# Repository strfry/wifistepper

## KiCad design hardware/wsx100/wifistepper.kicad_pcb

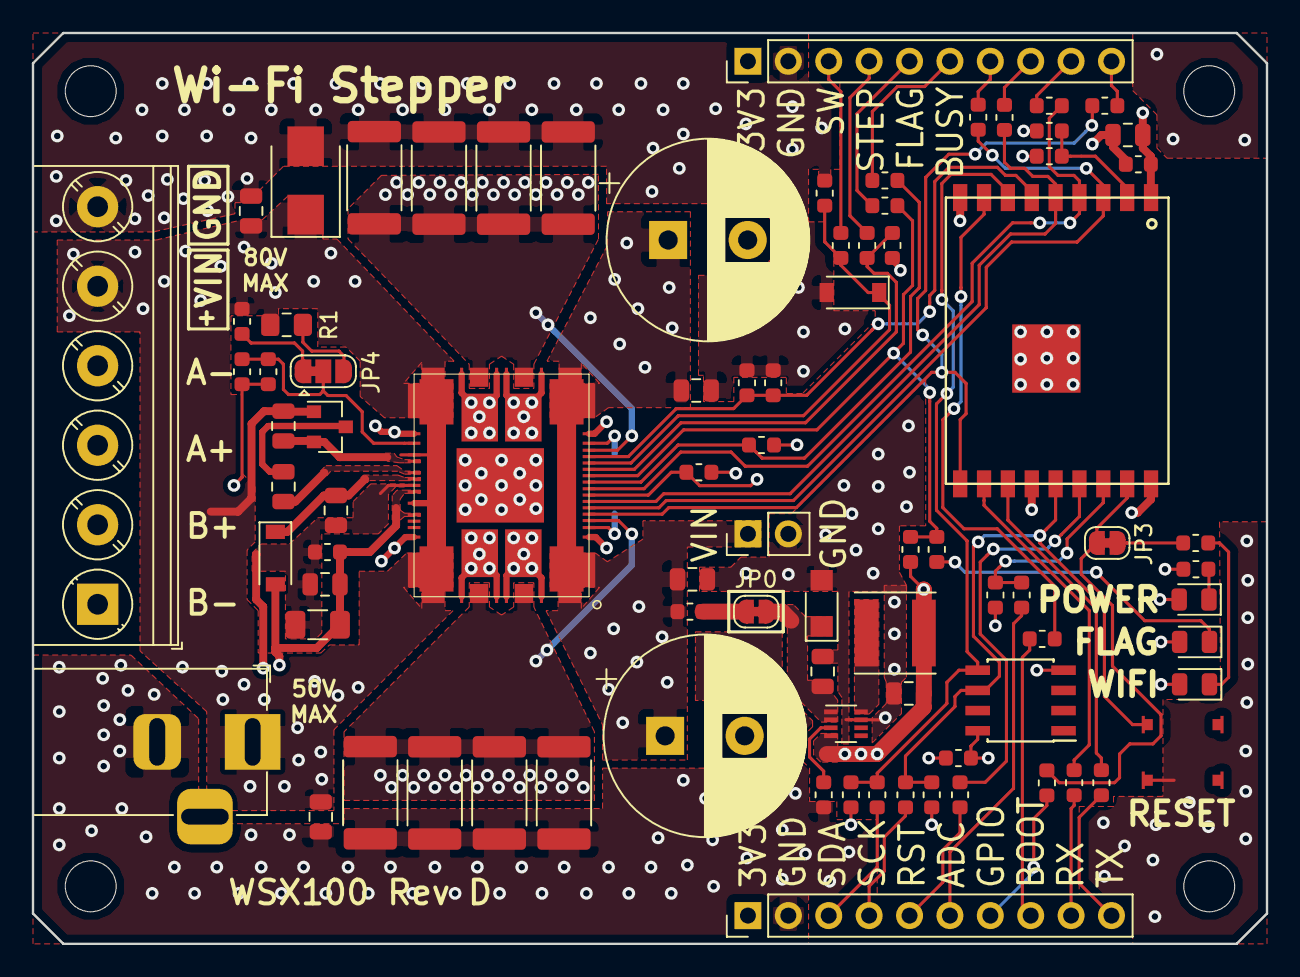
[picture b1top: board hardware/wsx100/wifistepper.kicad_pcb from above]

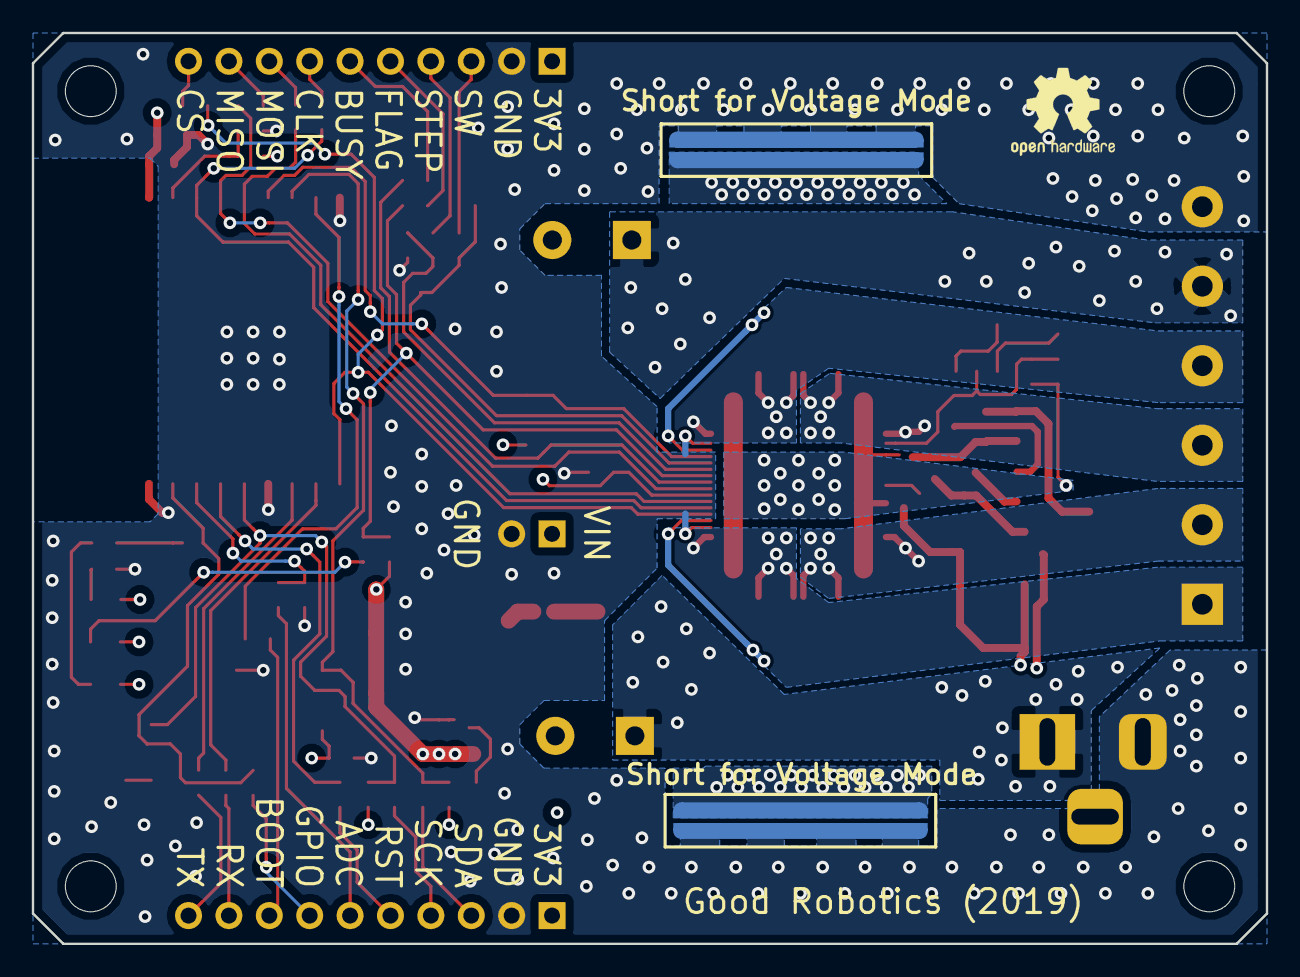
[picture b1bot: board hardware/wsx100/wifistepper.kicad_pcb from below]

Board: 4 copper layers, 77.6 x 57.3 mm, 86 parts (2 on the bottom side), 58 nets.

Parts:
C1: 22uF; C_1206_3216Metric
C2, C3: 470nF 100V; C_0805_2012Metric
C4: 220nF; C_0805_2012Metric
C5, C12, C14, C16, C17, C21, C22, C23, C24: 0.1uF; C_0603_1608Metric
C6, C7, C8, C9: 220nF 100V; C_0805_2012Metric
C10, C11: 100uF 100V (Low ESR); CP_Radial_D12.5mm_P5.00mm
C13: 47nF 100V; C_0805_2012Metric
C15, C20: 10uF; C_0805_2012Metric
C18: 1uF 100V; C_0805_2012Metric
C19: 1uF; C_0603_1608Metric
D0: 80V (Back EMF Clamp); D_SMB
D1: D_Schottky_x2_Serial_AKC; SOT-23
D2: D_Schottky; D_SOD-123
D3: LED GRN; D_0805_2012Metric
D4: LED YEL; D_0805_2012Metric
D5: LED RED; D_0805_2012Metric
D6: 3.9V; D_SOD-123
D7: 50V Clamp; D_SMF_DO-219AB
FB1: Ferrite_Bead_Small; L_0603_1608Metric
J1: Barrel_Jack_Switch; BarrelJack_Horizontal
J2: Screw_Terminal; TerminalBlock_Phoenix_PT-1,5-6-5.0-H_1x06_P5.00mm_Horizontal
J3, J4: Conn_01x10; PinHeader_1x10_P2.54mm_Vertical
J5: Conn_01x02; PinHeader_1x02_P2.54mm_Vertical
JP0, JP3: SolderJumper_2_Bridged; SolderJumper-2_P1.3mm_Bridged_RoundedPad1.0x1.5mm
JP1, JP2: Jumper_2_Open; STpowerSTEP01_JMP
JP4: SolderJumper_3_Bridged12; SolderJumper-3_P1.3mm_Bridged12_RoundedPad1.0x1.5mm
L1: 33uH; L_Taiyo-Yuden_NR-50xx
R1: -; Resistor_NP_0805
R2, R16, R17, R18, R19, R20, R21, R23, R24, R25, R26, R27, R28, R29: 22; R_0603_1608Metric
R3: 47K; R_0603_1608Metric
R4: 1.8K; R_0603_1608Metric
R5, R14, R15: 2.2K; R_0603_1608Metric
R6, R22: 1K; R_0603_1608Metric
R7, R8: 39K; R_0603_1608Metric
R9, R10, R11: 330; R_0603_1608Metric
R12, R13: 10K; R_0603_1608Metric
RS1, RS2, RS3, RS4, RS5, RS6, RS7, RS8: 0.27; R_2512_6332Metric
SW1: SW_SPST; TL3315NF100Q
U1: ESP-WROOM-02
U2: powerSTEP01
U3: MAX15062A; DFN-8_2x2mm_P0.5mm
U4: ATECC508A; SOIC-8_3.9x4.9mm_P1.27mm

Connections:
+3V3: C1.1, C4.1, C12.1, C15.1, C16.1, C20.1, C21.2, C22.1, D2.2, D3.2, D4.2, D5.2, J3.1, J4.1, L1.1, R7.1, R8.1, R13.2, R14.1, R15.1, U1.1, U2.13, U2.60, U2.62, U3.4, U4.8
AUTH_SCK: R15.2, R27.2, SW1.2, U1.14, U4.6
AUTH_SDA: R14.2, R26.2, U1.7, U4.5
GND: C1.2, C2.2, C4.2, C5.2, C6.2, C7.2, C8.2, C9.2, C10.2, C11.2, C12.2, C14.2, C15.2, C16.2, C17.2, C18.2, C19.2, C20.2, C21.1, C22.2, C23.2, C24.2, D0.2, D6.2, D7.2, J1.2, J2.6, J3.2, J4.2, J5.2, JP1.2, JP2.2, R4.2, R6.2, R11.2, R12.2, RS1.1, RS2.1, RS3.1, RS4.1, RS5.1, RS6.1, RS7.1, RS8.1, SW1.1, U1.9, U1.13, U1.18, U1.19, U2.8, U2.21, U2.59, U2.E9, U3.7, U4.4
unnamed: C2.1, D2.1, U2.58
unnamed: C3.1, D1.2, U2.56
unnamed: C13.1, U2.57
unnamed: C13.2, D1.3
unnamed: C17.1, R13.1, U1.2
unnamed: C18.1, D7.1, JP0.2, U3.1, U3.2
unnamed: C19.1, U3.3
unnamed: D3.1, R11.1
unnamed: D4.1, R10.1
unnamed: D5.1, R9.1
unnamed: FB1.2, JP0.1
unnamed: J3.3, R22.1
unnamed: J3.4, R23.1
unnamed: J3.5, R24.1
unnamed: J3.6, R25.1
unnamed: J3.7, R16.1
unnamed: J3.8, R17.1
unnamed: J3.9, R2.1
unnamed: J3.10, R29.1
unnamed: J4.3, R26.1
unnamed: J4.4, R27.1
unnamed: J4.5, R18.1
unnamed: J4.6, R5.1
unnamed: J4.7, R19.1
unnamed: J4.8, R28.1
unnamed: J4.9, R20.1
unnamed: J4.10, R21.1
unnamed: JP1.1, RS1.2, RS2.2, RS3.2, RS7.2, U2.20, U2.E10, U2.E11
unnamed: JP2.1, RS4.2, RS5.2, RS6.2, RS8.2, U2.9, U2.E12, U2.E13
unnamed: JP4.1, R3.2
unnamed: JP4.3, R1.2
unnamed: L1.2, U3.8
OUTA1: J2.3, U2.38, U2.42, U2.53, U2.E4
OUTA2: J2.4, U2.22, U2.33, U2.37, U2.E3
OUTB1: J2.2, U2.65, U2.76, U2.80, U2.E7
OUTB2: J2.1, U2.7, U2.81, U2.85, U2.E8
PROG_BOOT: R28.2, U1.8
PROG_RX: R20.2, U1.11
PROG_TX: R21.2, U1.12
SM_ADC: C5.1, JP4.2, R4.1, U2.54
SM_BUSY: R7.2, R25.2, U2.15
SM_CLK: R16.2, U1.3, U2.11
SM_CS: R29.2, U1.10, U2.10
SM_FLAG: R8.2, R9.2, R24.2, U2.16
SM_RST: C14.1, R12.1, U1.6, U2.19
SM_SI: R17.2, U1.5, U2.12
SM_SO: R2.2, U1.4, U2.14
SM_STCLK: C24.1, R23.2, U2.17
SM_SW: C23.1, D6.1, R22.2, U2.18
VIN: C3.2, C6.1, C7.1, C8.1, C9.1, C10.1, C11.1, D0.1, D1.1, FB1.1, J1.1, J2.5, J5.1, R1.1, R3.1, U2.55, U2.61, U2.E1, U2.E2, U2.E5, U2.E6
WIFI_ADC: R5.2, R6.1, U1.16
WIFI_CONN: JP3.1, R10.2
WIFI_GPIO: JP3.2, R19.2, U1.17
WIFI_RST: R18.2, U1.15

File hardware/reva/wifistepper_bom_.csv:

Component,Description,Part,References,Value,Footprint,Quantity Per PCB,Datasheet
1,Unpolarized capacitor,C,C5 C12 C14 C16 C17 C21,0.1uF,C_0603_1608Metric,6,~
2,Unpolarized capacitor,C,C15 C20,10uF,C_0805_2012Metric,2,~
3,Unpolarized capacitor,C,C19,1uF,C_0603_1608Metric,1,~
4,Unpolarized capacitor,C,C18,1uF 100V,C_1206_3216Metric,1,~
5,Unpolarized capacitor,C,C4,220nF,C_0805_2012Metric,1,~
6,Unpolarized capacitor,C,C6 C7 C8 C9,220nF 100V,C_0805_2012Metric,4,~
7,Polarised capacitor,CP,C1,22uF,C_1206_3216Metric,1,~
8,Unpolarized capacitor,C,C2 C3,470nF 100V,C_0805_2012Metric,2,~
9,Unpolarized capacitor,C,C13,47nF 100V,C_0805_2012Metric,1,~
10,Polarised capacitor,CP,C10 C11,68uF 100V,Capacitor_SMD-Panasonic_H13,2,~
11,Schottky diode,D_Schottky,D2,D_Schottky,D_SOD-123,1,~
12,Dual schottky diode,D_Schottky_x2_Serial_AKC,D1,D_Schottky_x2_Serial_AKC,SOT-23,1,~
13,LED generic,LED,D3,LED GRN,D_0805_2012Metric,1,~
14,LED generic,LED,D5,LED RED,D_0805_2012Metric,1,~
15,LED generic,LED,D4,LED YEL,D_0805_2012Metric,1,~
16,DC Barrel Jack with an internal switch,Barrel_Jack_Switch,J1,Barrel_Jack_Switch,BarrelJack_Horizontal,1,~
17,"Generic connector, single row, 01x04, script generated (kicad-library-utils/schlib/autogen/connector/)",Conn_01x04,J5,Conn_01x04,PinHeader_1x04_P2.54mm_Vertical,1,~
18,"Generic connector, single row, 01x06, script generated (kicad-library-utils/schlib/autogen/connector/)",Conn_01x06,J3 J4,Conn_01x06,PinHeader_1x06_P2.54mm_Vertical,2,~
19,"Generic screw terminal, single row, 01x06, script generated (kicad-library-utils/schlib/autogen/connector/)",Screw_Terminal_01x06,J2,Screw_Terminal,"Phoenix_Screw_Terminal-MKDS_1,6-P3.81x06",1,~
20,Inductor,L,L1,33uH,L_Taiyo-Yuden_NR-50xx,1,~
21,Resistor,R,R3 R4 R5 R6,0.2,R_2512_6332Metric,4,~
22,Resistor,R,R0,00,R_0805_2012Metric_Pad1.15x1.40mm_HandSolder,1,~
23,Resistor,R,R2,1.8K,R_0603_1608Metric,1,~
24,Resistor,R,R12 R13,10K,R_0603_1608Metric,2,~
25,Resistor,R,R9 R10 R11,330,R_0603_1608Metric,3,~
26,Resistor,R,R7 R8,39K,R_0603_1608Metric,2,~
27,Resistor,R,R14 R15,4.7K,R_0603_1608Metric,2,~
28,Resistor,R,R1,47K,R_0603_1608Metric,1,~
29,,ATECC508A,U4,ATECC508A,SOIC-8_3.9x4.9mm_P1.27mm,1,
30,,ESP-WROOM-02,U1,ESP-WROOM-02,ESP-WROOM-02,1,
31,"60V, 300mA, synchronous step-down dc-dc converter, 3.3V fixed output voltage, DFN-8",MAX15062A,U3,MAX15062A,DFN-8_2x2mm_P0.5mm,1,http://datasheets.maximintegrated.com/en/ds/MAX15062.pdf
32,,powerSTEP01,U2,powerSTEP01,powerSTEP01,1,





Component Groups:,32
Component Count:,52
Fitted Components:,52
Number of PCBs:,1
Total components:,52
Schematic Version:,
Schematic Date:,
BoM Date:,Sun 29 Jul 2018 12:20:27 PM PDT
Schematic Source:,/home/aklofas/Projects/wifistepper/wifistepper.sch
KiCad Version:,Eeschema 5.0.0-fee4fd1~65~ubuntu16.04.1

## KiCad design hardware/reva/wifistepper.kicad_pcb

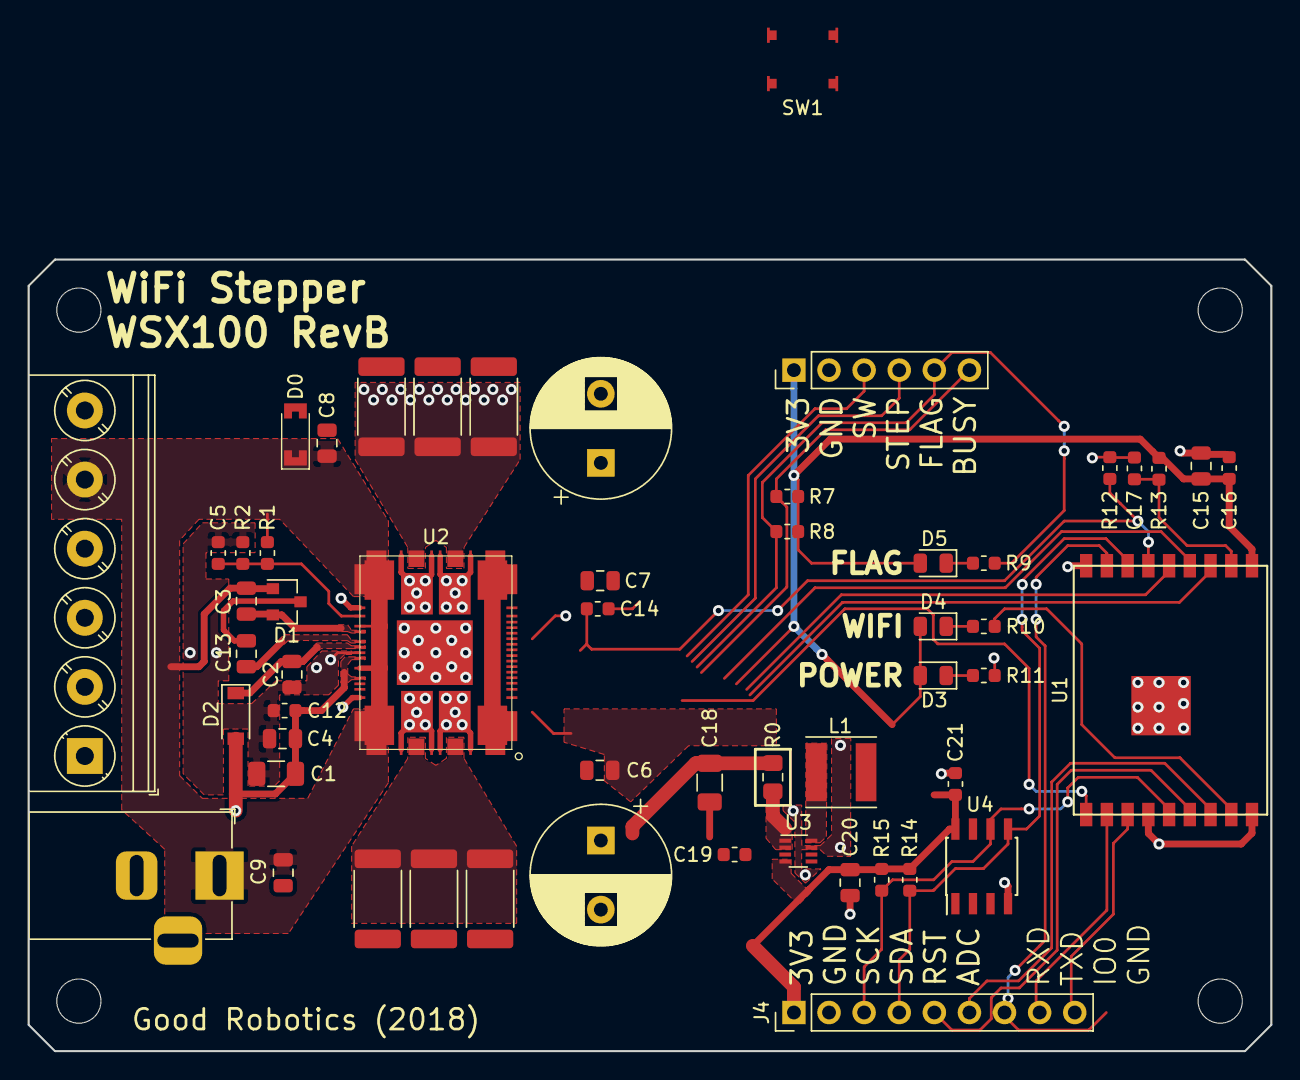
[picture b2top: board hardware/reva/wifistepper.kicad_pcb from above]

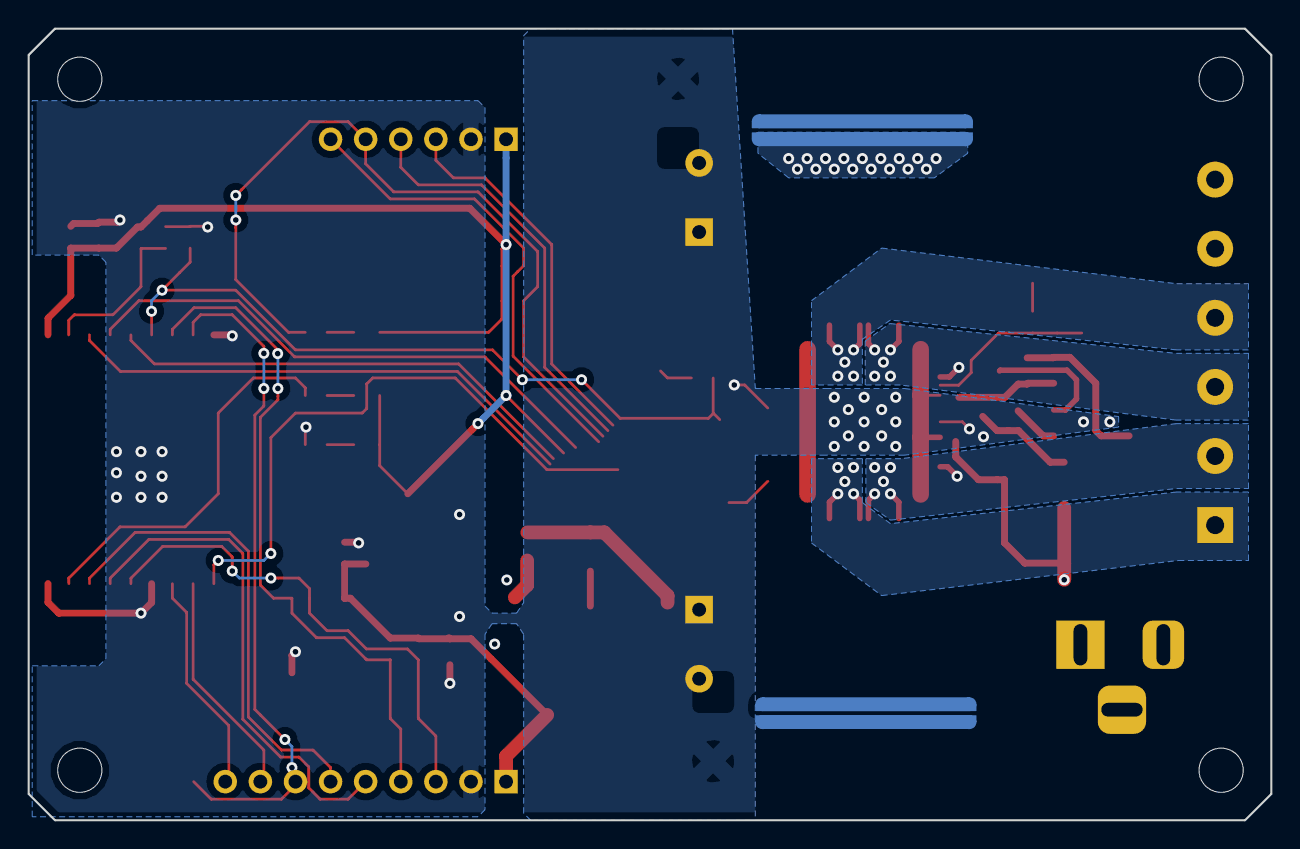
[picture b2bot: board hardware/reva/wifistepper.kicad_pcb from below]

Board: 2 copper layers, 89.9 x 57.3 mm, 57 parts (2 on the bottom side), 38 nets.

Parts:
C1: 22uF; C_1206_3216Metric
C2, C3: 470nF 100V; C_0805_2012Metric
C4: 220nF; C_0805_2012Metric
C5, C12, C14, C16, C17, C21: 0.1uF; C_0603_1608Metric
C6, C7, C8, C9: 220nF 100V; C_0805_2012Metric
C10, C11: 68uF 100V; CP_Radial_D10.0mm_P5.00mm
C13: 47nF 100V; C_0805_2012Metric
C15, C20: 10uF; C_0805_2012Metric
C18: 1uF 100V; C_1206_3216Metric
C19: 1uF; C_0603_1608Metric
D0: RPOL; D_SOD80
D1: D_Schottky_x2_Serial_AKC; SOT-23
D2: D_Schottky; D_SOD-123
D3: LED GRN; D_0805_2012Metric
D4: LED YEL; D_0805_2012Metric
D5: LED RED; D_0805_2012Metric
J1: Barrel_Jack_Switch; BarrelJack_Horizontal
J2: Screw_Terminal; TerminalBlock_Phoenix_PT-1,5-6-5.0-H_1x06_P5.00mm_Horizontal
J3: Conn_01x06; PinHeader_1x06_P2.54mm_Vertical
J4: Conn_01x09; PinHeader_1x09_P2.54mm_Vertical
JP1, JP2: Jumper_2_Open; STpowerSTEP01_JMP
L1: 33uH; L_Taiyo-Yuden_NR-50xx
R0: 00; R_0805_2012Metric_Pad1.15x1.40mm_HandSolder
R1: 47K; R_0603_1608Metric
R2: 1.8K; R_0603_1608Metric
R7, R8: 39K; R_0603_1608Metric
R9, R10, R11: 330; R_0603_1608Metric
R12, R13: 10K; R_0603_1608Metric
R14, R15: 4.7K; R_0603_1608Metric
RS1, RS2, RS3, RS4, RS5, RS6: 0.06; R_2512_6332Metric
SW1: SW_SPST; TL3315NF100Q
U1: ESP-WROOM-02
U2: powerSTEP01
U3: MAX15062A; DFN-8_2x2mm_P0.5mm
U4: ATECC508A; SOIC-8_3.9x4.9mm_P1.27mm

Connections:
+3V3: C1.1, C4.1, C12.1, C15.1, C16.1, C20.1, C21.2, D2.2, D3.2, D4.2, D5.2, J3.1, J4.1, L1.1, R7.1, R8.1, R13.2, R14.1, R15.1, U1.1, U2.13, U2.60, U2.62, U3.4, U4.8
AUTH_SCK: J4.3, R15.2, U1.14, U4.6
AUTH_SDA: J4.4, R14.2, SW1.2, U1.7, U4.5
GND: C1.2, C2.2, C4.2, C5.2, C6.2, C7.2, C8.2, C9.2, C10.2, C11.2, C12.2, C14.2, C15.2, C16.2, C17.2, C18.2, C19.2, C20.2, C21.1, D0.2, J1.2, J2.6, J3.2, J4.2, JP1.2, JP2.2, R2.2, R11.2, R12.2, RS1.1, RS2.1, RS3.1, RS4.1, RS5.1, RS6.1, SW1.1, U1.9, U1.13, U1.18, U1.19, U2.8, U2.21, U2.59, U2.E9, U3.7, U4.4
unnamed: C2.1, D2.1, U2.58
unnamed: C3.1, D1.2, U2.56
unnamed: C13.1, U2.57
unnamed: C13.2, D1.3
unnamed: C17.1, R13.1, U1.2
unnamed: C19.1, U3.3
unnamed: D3.1, R11.1
unnamed: D4.1, R10.1
unnamed: D5.1, R9.1
unnamed: JP1.1, RS1.2, RS2.2, RS3.2, U2.20, U2.E10, U2.E11
unnamed: JP2.1, RS4.2, RS5.2, RS6.2, U2.9, U2.E12, U2.E13
unnamed: L1.2, U3.8
unnamed: R0.1, U3.1, U3.2
OUTA1: J2.3, U2.38, U2.42, U2.53, U2.E4
OUTA2: J2.4, U2.22, U2.33, U2.37, U2.E3
OUTB1: J2.2, U2.65, U2.76, U2.80, U2.E7
OUTB2: J2.1, U2.7, U2.81, U2.85, U2.E8
PROG_BOOT: J4.7, U1.8
PROG_RX: J4.8, U1.11
PROG_TX: J4.9, U1.12
SM_ADC: C5.1, R1.2, R2.1, U2.54
SM_BUSY: J3.6, R7.2, U2.15
SM_CLK: U1.3, U2.11
SM_CS: U1.10, U2.10
SM_FLAG: J3.5, R8.2, R9.2, U2.16
SM_RST: C14.1, R12.1, U1.6, U2.19
SM_SI: U1.5, U2.12
SM_SO: U1.4, U2.14
SM_STCLK: J3.4, U2.17
SM_SW: J3.3, U2.18
VIN: C3.2, C6.1, C7.1, C8.1, C9.1, C10.1, C11.1, C18.1, D0.1, D1.1, J1.1, J2.5, R0.2, R1.1, U2.55, U2.61, U2.E1, U2.E2, U2.E5, U2.E6
WIFI_ADC: J4.5, U1.16
WIFI_CONN: R10.2, U1.17
WIFI_RST: J4.6, U1.15

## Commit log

2018-08-06 Board revA
2018-09-16 Initial SW to control powerstep01
2018-09-17 Most of powerstep01 library written. Needs testing
2018-09-18 More tweaks on powerstep01 library
2018-09-23 Organized revA board and added powerstep01 breakout to repo
2018-10-24 Webpage development, rework of RevA
2018-10-29 Rev B design complete
2018-11-20 Started Json Api
2018-11-20 Webpage update
2018-11-21 Started motor json api
2018-11-22 More webpage development
2018-11-22 More api development
2018-12-06 Firmware update
2018-12-06 WebUI Update
2018-12-07 Updated WebUI
2018-12-22 Updated firmware
2018-12-22 Updated hardware and webpage
2019-02-05 Updated hardware to revD (still WIP)
2019-02-06 Updated Rev D
2019-02-07 final tweaks on Rev D
2019-02-07 Nearing final Rev D
2019-02-08 finalized rev d
2019-03-17 Started MQTT integration
2019-03-18 Added command queue and started daisy chaining support
2019-03-18 Updated board layout
2019-03-19 Working on command queue
2019-03-20 Updated hardware to rev d2
2019-03-20 Checkpoint for command/daisy buffers
2019-03-22 Refactored to make unified config and state structures
2019-03-23 checkpoint for daisy parsing
2019-03-23 checkpoint
2019-03-24 daisy feature almost complete
2019-03-25 lowtcp and python interface
2019-04-15 worked on command queue and lowtcp
2019-04-16 Added update mechanism
2019-04-19 update ecc code
2019-04-24 worked on python library
2019-04-30 Started crypto library
2019-05-01 Worked on crypto
2019-05-02 Crypto library nearing completion
2019-05-19 Updated doc
2019-05-20 mfg testing
2019-06-01 documentation update
2019-06-09 various compiles fixes for esp32
2019-06-09 pinning from IHM03A
2019-06-09 port update.cpp
2019-06-09 format filesystem on mount error
2019-06-09 revert system reset pin
